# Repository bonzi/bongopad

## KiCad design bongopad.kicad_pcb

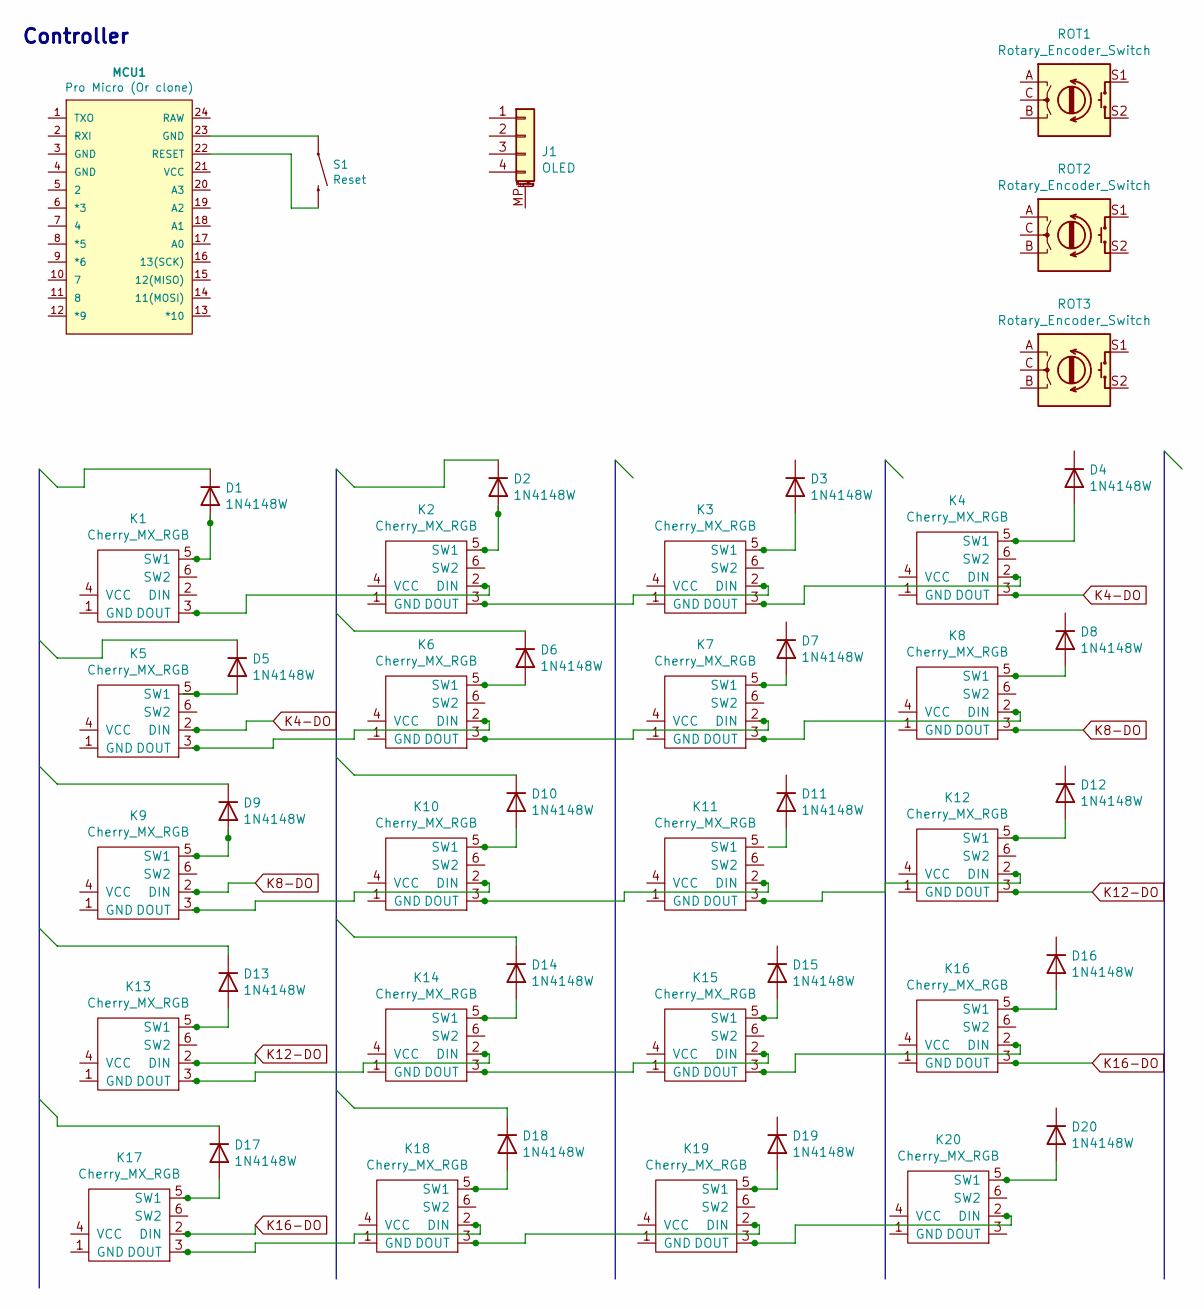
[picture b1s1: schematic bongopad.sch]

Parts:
D1, D2, D3, D4, D5, D6, D7, D8, D9, D10, D11, D12, D13, D14, D15, D16, D17, D18, D19, D20: 1N4148W; D_SOD-123
J1: OLED; PinHeader_1x4_P2.54mm_Vertical
K1, K2, K3, K4, K5, K6, K7, K8, K9, K10, K11, K12, K13, K14, K15, K16, K17, K18, K19, K20: Cherry_MX_RGB; Cherry-MX_PCB-Mounted_LTST-A683CEGBW_Kailh_Socket
MCU1: Pro Micro (Or clone); SPARKFUN_PRO_MICRO
ROT1, ROT2, ROT3: Rotary_Encoder_Switch; RotaryEncoder_Alps_EC11E-Switch_Vertical_H20mm
S1: Reset; TACTILE_SWITCH_PTH_6.0MM

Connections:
K4-DO: K4.3 (DOUT), K5.2 (DIN)
K8-DO: K8.3 (DOUT), K9.2 (DIN)
K12-DO: K12.3 (DOUT), K13.2 (DIN)
K16-DO: K16.3 (DOUT), K17.2 (DIN)
unnamed: D1.2 (A), K1.5 (SW1)
unnamed: D2.2 (A), K2.5 (SW1)
unnamed: D3.2 (A), K3.5 (SW1)
unnamed: D4.2 (A), K4.5 (SW1)
unnamed: D5.2 (A), K5.5 (SW1)
unnamed: D6.2 (A), K6.5 (SW1)
unnamed: D7.2 (A), K7.5 (SW1)
unnamed: D8.2 (A), K8.5 (SW1)
unnamed: D9.2 (A), K9.5 (SW1)
unnamed: D10.2 (A), K10.5 (SW1)
unnamed: D12.2 (A), K12.5 (SW1)
unnamed: D13.2 (A), K13.5 (SW1)
unnamed: D14.2 (A), K14.5 (SW1)
unnamed: D15.2 (A), K15.5 (SW1)
unnamed: D16.2 (A), K16.5 (SW1)
unnamed: D17.2 (A), K17.5 (SW1)
unnamed: D18.2 (A), K18.5 (SW1)
unnamed: D19.2 (A), K19.5 (SW1)
unnamed: D20.2 (A), K20.5 (SW1)
unnamed: K1.3 (DOUT), K2.2 (DIN)
unnamed: K2.3 (DOUT), K3.2 (DIN)
unnamed: K3.3 (DOUT), K4.2 (DIN)
unnamed: K5.3 (DOUT), K6.2 (DIN)
unnamed: K6.3 (DOUT), K7.2 (DIN)
unnamed: K7.3 (DOUT), K8.2 (DIN)
unnamed: K9.3 (DOUT), K10.2 (DIN)
unnamed: K10.3 (DOUT), K11.2 (DIN)
unnamed: K11.3 (DOUT), K12.2 (DIN)
unnamed: K13.3 (DOUT), K14.2 (DIN)
unnamed: K14.3 (DOUT), K15.2 (DIN)
unnamed: K15.3 (DOUT), K16.2 (DIN)
unnamed: K17.3 (DOUT), K18.2 (DIN)
unnamed: K18.3 (DOUT), K19.2 (DIN)
unnamed: K19.3 (DOUT), K20.2 (DIN)
unnamed: MCU1.22 (RESET), S1.3 (2)
unnamed: MCU1.23 (GND), S1.1

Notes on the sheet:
Controller

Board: 2 copper layers, 46 parts (20 on the bottom side), 40 nets, no tracks yet.

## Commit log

2021-08-17 Use CC BY-SA 4.0
